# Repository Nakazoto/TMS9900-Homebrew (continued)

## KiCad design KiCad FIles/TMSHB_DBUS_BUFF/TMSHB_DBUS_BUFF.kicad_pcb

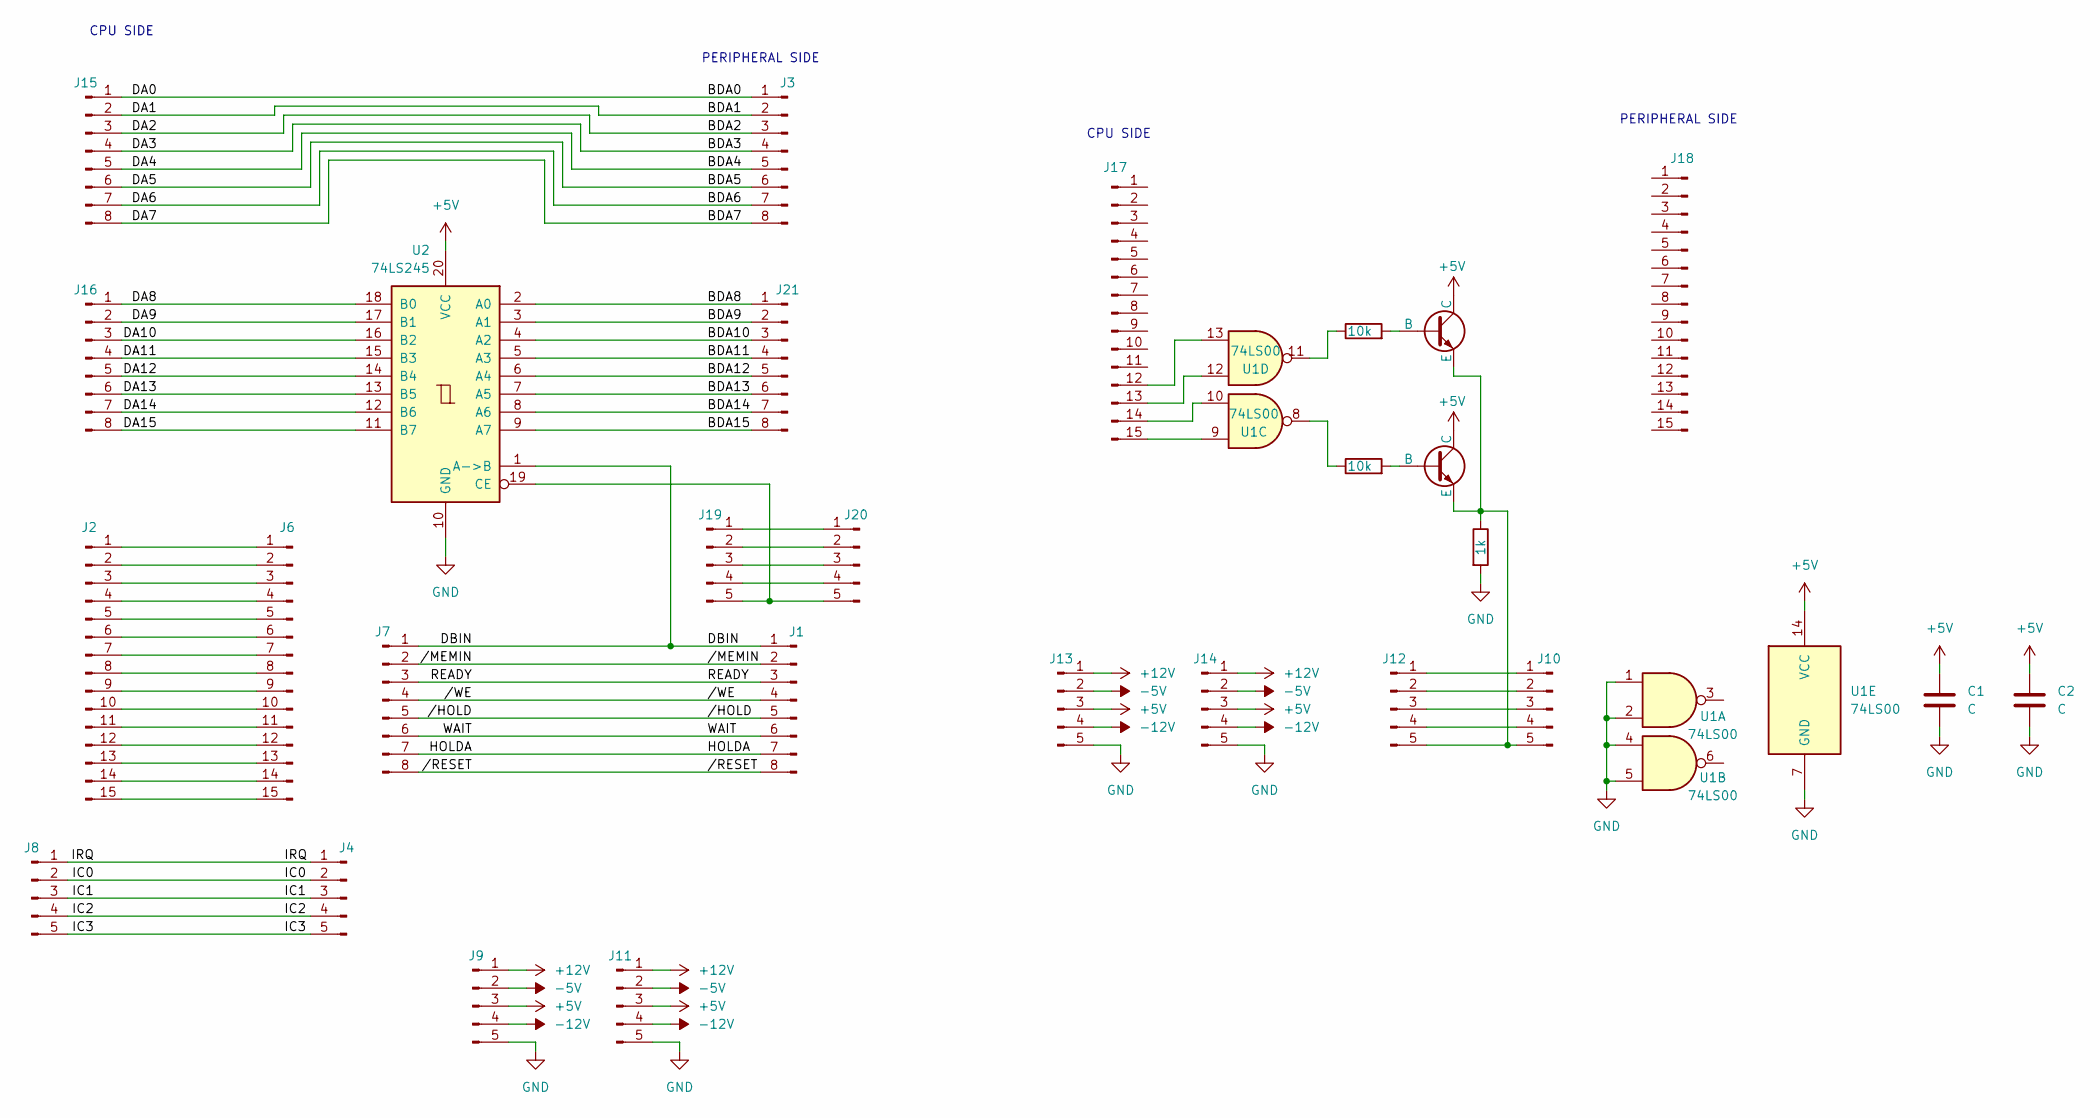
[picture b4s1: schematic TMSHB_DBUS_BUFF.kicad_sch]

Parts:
C1, C2: C; C_Disc_D3.0mm_W1.6mm_P2.50mm
J1, J3, J7, J15, J16, J21: Conn_01x08_Pin; PinHeader_1x08_P2.54mm_Vertical
J2, J6, J17, J18: Conn_01x15_Pin; PinHeader_1x15_P2.54mm_Vertical
J4, J8, J9, J10, J11, J12, J13, J14, J19, J20: Conn_01x05_Pin; PinHeader_1x05_P2.54mm_Vertical
Q1, Q3: NPN; TO-92_Inline_Wide
R1: 1k; R_Axial_DIN0207_L6.3mm_D2.5mm_P10.16mm_Horizontal
R2, R3: 10k; R_Axial_DIN0207_L6.3mm_D2.5mm_P10.16mm_Horizontal
U1: 74LS00; DIP-14_W7.62mm
U2: 74LS245; DIP-20_W7.62mm

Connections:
+5V: C1.1, C2.1, J9.3, J11.3, J13.3, J14.3, Q1.1 (C), Q3.1 (C), U1.14 (VCC), U2.20 (VCC)
+12V: J9.1, J11.1, J13.1, J14.1
-5V: J9.2, J11.2, J13.2, J14.2
-12V: J9.4, J11.4, J13.4, J14.4
/BDA0: J3.1, J15.1
/BDA1: J3.2, J15.2
/BDA2: J3.3, J15.3
/BDA3: J3.4, J15.4
/BDA4: J3.5, J15.5
/BDA5: J3.6, J15.6
/BDA6: J3.7, J15.7
/BDA7: J3.8, J15.8
/BDA8: J21.1, U2.2 (A0)
/BDA9: J21.2, U2.3 (A1)
/BDA10: J21.3, U2.4 (A2)
/BDA11: J21.4, U2.5 (A3)
/BDA12: J21.5, U2.6 (A4)
/BDA13: J21.6, U2.7 (A5)
/BDA14: J21.7, U2.8 (A6)
/BDA15: J21.8, U2.9 (A7)
/DA8: J16.1, U2.18 (B0)
/DA9: J16.2, U2.17 (B1)
/DA10: J16.3, U2.16 (B2)
/DA11: J16.4, U2.15 (B3)
/DA12: J16.5, U2.14 (B4)
/DA13: J16.6, U2.13 (B5)
/DA14: J16.7, U2.12 (B6)
/DA15: J16.8, U2.11 (B7)
/DBIN: J1.1, J7.1, U2.1 (A->B)
/HOLDA: J1.7, J7.7
/IC0: J4.2, J8.2
/IC1: J4.3, J8.3
/IC2: J4.4, J8.4
/IC3: J4.5, J8.5
/IRQ: J4.1, J8.1
/READY: J1.3, J7.3
/WAIT: J1.6, J7.6
//HOLD: J1.5, J7.5
//MEMIN: J1.2, J7.2
//RESET: J1.8, J7.8
//WE: J1.4, J7.4
GND: C1.2, C2.2, J9.5, J11.5, J13.5, J14.5, R1.2, U1.1, U1.2, U1.4, U1.5, U1.7 (GND), U2.10 (GND)
unnamed: J2.1, J6.1
unnamed: J2.2, J6.2
unnamed: J2.3, J6.3
unnamed: J2.4, J6.4
unnamed: J2.5, J6.5
unnamed: J2.6, J6.6
unnamed: J2.7, J6.7
unnamed: J2.8, J6.8
unnamed: J2.9, J6.9
unnamed: J2.10, J6.10
unnamed: J2.11, J6.11
unnamed: J2.12, J6.12
unnamed: J2.13, J6.13
unnamed: J2.14, J6.14
unnamed: J2.15, J6.15
unnamed: J10.1, J12.1
unnamed: J10.2, J12.2
unnamed: J10.3, J12.3
unnamed: J10.4, J12.4
unnamed: J10.5, J12.5, Q1.3 (E), Q3.3 (E), R1.1
unnamed: J17.12, U1.13
unnamed: J17.13, U1.12
unnamed: J17.14, U1.10
unnamed: J17.15, U1.9
unnamed: J19.1, J20.1
unnamed: J19.2, J20.2
unnamed: J19.3, J20.3
unnamed: J19.4, J20.4
unnamed: J19.5, J20.5, U2.19 (CE)
unnamed: Q1.2 (B), R3.2
unnamed: Q3.2 (B), R2.2
unnamed: R2.1, U1.11
unnamed: R3.1, U1.8

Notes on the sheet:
PERIPHERAL SIDE
CPU SIDE

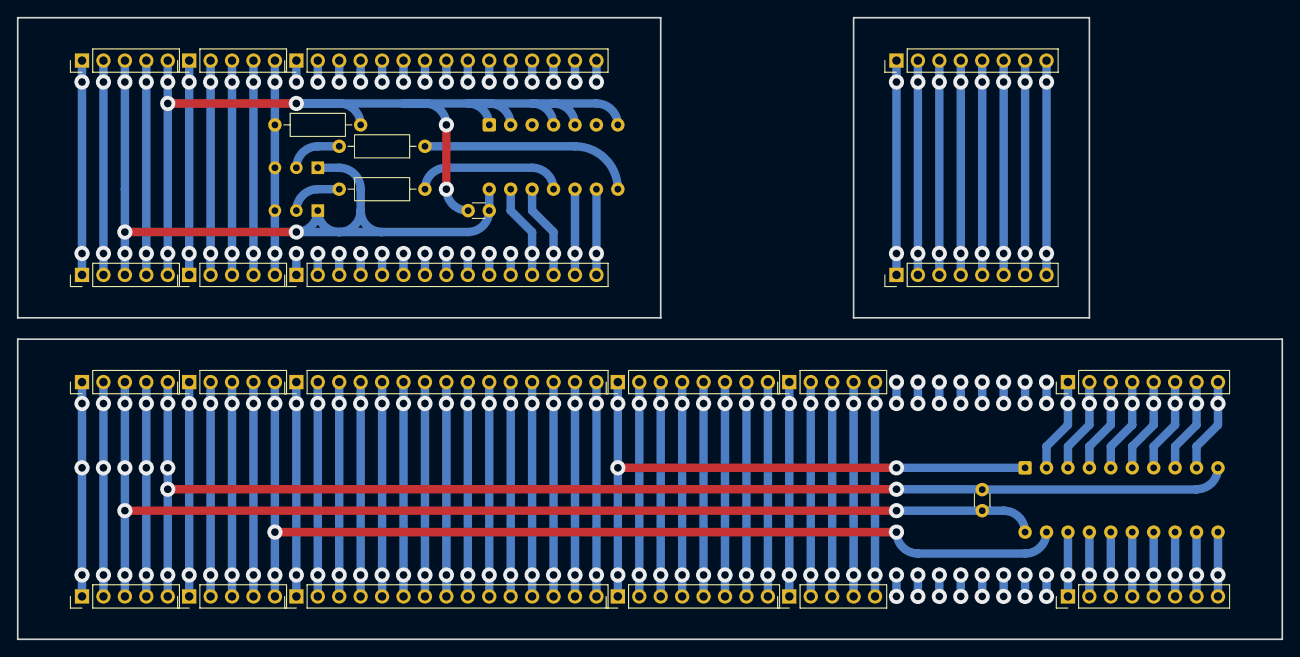
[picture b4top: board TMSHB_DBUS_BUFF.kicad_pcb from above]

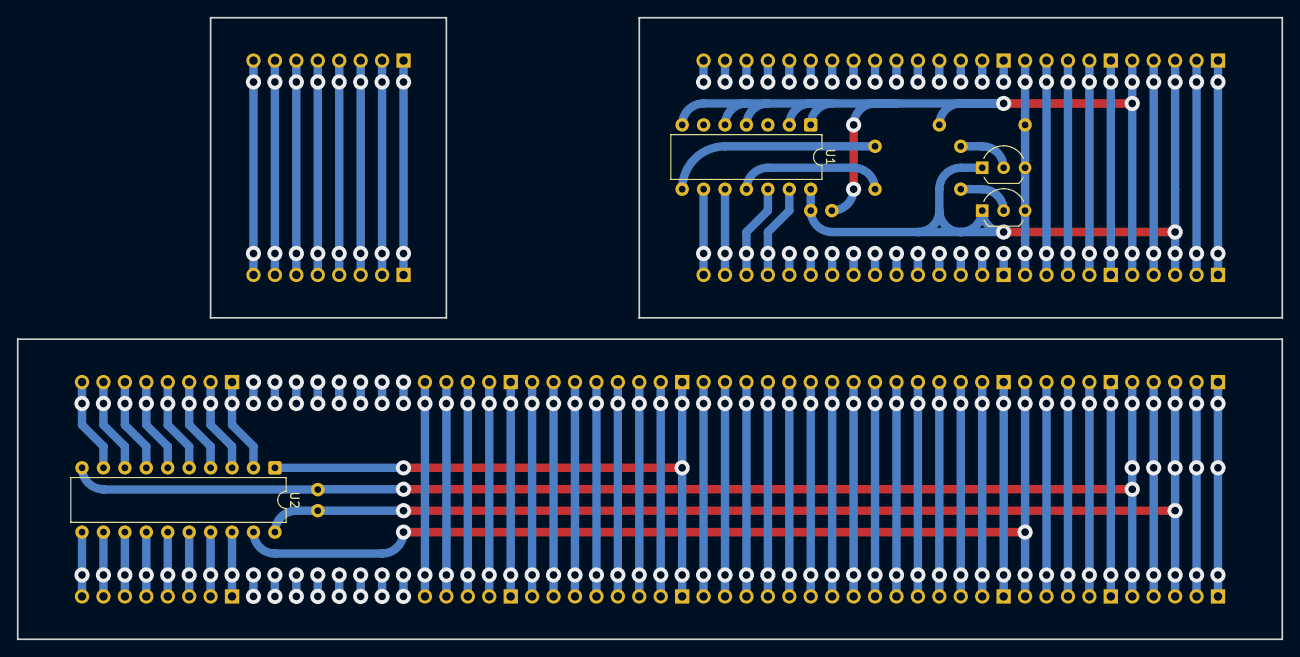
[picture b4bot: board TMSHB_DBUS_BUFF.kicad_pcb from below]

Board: 2 copper layers, 149.9 x 73.7 mm, 29 parts (4 on the bottom side), 75 nets.

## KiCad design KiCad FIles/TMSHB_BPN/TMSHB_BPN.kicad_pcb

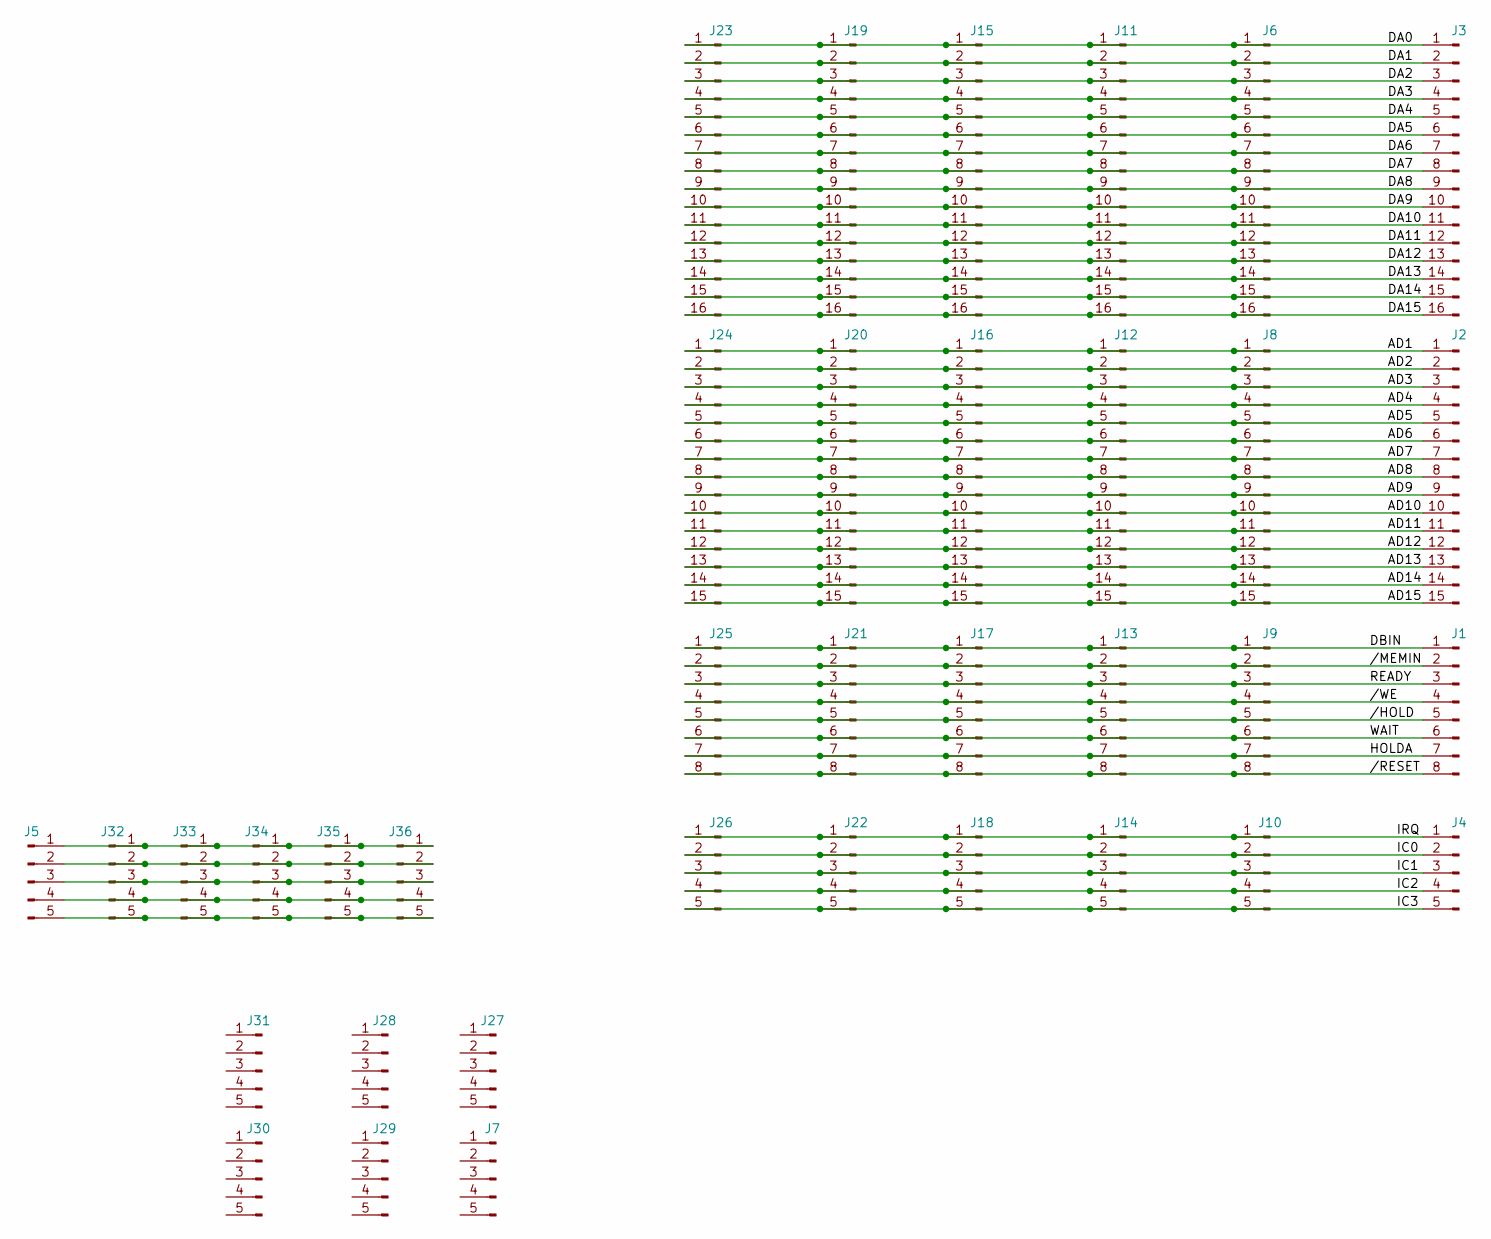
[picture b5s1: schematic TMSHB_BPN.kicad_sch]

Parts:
J1, J9, J13, J17, J21, J25: Conn_01x08_Pin; PinHeader_1x08_P2.54mm_Vertical
J2, J8, J12, J16, J20, J24: Conn_01x15_Pin; PinHeader_1x15_P2.54mm_Vertical
J3, J6, J11, J15, J19, J23: Conn_01x16_Pin; PinHeader_1x16_P2.54mm_Vertical
J4, J5, J7, J10, J14, J18, J22, J26, J27, J28, J29, J30, J31, J32, J33, J34, J35, J36: Conn_01x05_Pin; PinHeader_1x05_P2.54mm_Vertical

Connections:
/AD1: J2.1, J8.1, J12.1, J16.1, J20.1, J24.1
/AD2: J2.2, J8.2, J12.2, J16.2, J20.2, J24.2
/AD3: J2.3, J8.3, J12.3, J16.3, J20.3, J24.3
/AD4: J2.4, J8.4, J12.4, J16.4, J20.4, J24.4
/AD5: J2.5, J8.5, J12.5, J16.5, J20.5, J24.5
/AD6: J2.6, J8.6, J12.6, J16.6, J20.6, J24.6
/AD7: J2.7, J8.7, J12.7, J16.7, J20.7, J24.7
/AD8: J2.8, J8.8, J12.8, J16.8, J20.8, J24.8
/AD9: J2.9, J8.9, J12.9, J16.9, J20.9, J24.9
/AD10: J2.10, J8.10, J12.10, J16.10, J20.10, J24.10
/AD11: J2.11, J8.11, J12.11, J16.11, J20.11, J24.11
/AD12: J2.12, J8.12, J12.12, J16.12, J20.12, J24.12
/AD13: J2.13, J8.13, J12.13, J16.13, J20.13, J24.13
/AD14: J2.14, J8.14, J12.14, J16.14, J20.14, J24.14
/AD15: J2.15, J8.15, J12.15, J16.15, J20.15, J24.15
/DA0: J3.1, J6.1, J11.1, J15.1, J19.1, J23.1
/DA1: J3.2, J6.2, J11.2, J15.2, J19.2, J23.2
/DA2: J3.3, J6.3, J11.3, J15.3, J19.3, J23.3
/DA3: J3.4, J6.4, J11.4, J15.4, J19.4, J23.4
/DA4: J3.5, J6.5, J11.5, J15.5, J19.5, J23.5
/DA5: J3.6, J6.6, J11.6, J15.6, J19.6, J23.6
/DA6: J3.7, J6.7, J11.7, J15.7, J19.7, J23.7
/DA7: J3.8, J6.8, J11.8, J15.8, J19.8, J23.8
/DA8: J3.9, J6.9, J11.9, J15.9, J19.9, J23.9
/DA9: J3.10, J6.10, J11.10, J15.10, J19.10, J23.10
/DA10: J3.11, J6.11, J11.11, J15.11, J19.11, J23.11
/DA11: J3.12, J6.12, J11.12, J15.12, J19.12, J23.12
/DA12: J3.13, J6.13, J11.13, J15.13, J19.13, J23.13
/DA13: J3.14, J6.14, J11.14, J15.14, J19.14, J23.14
/DA14: J3.15, J6.15, J11.15, J15.15, J19.15, J23.15
/DA15: J3.16, J6.16, J11.16, J15.16, J19.16, J23.16
/DBIN: J1.1, J9.1, J13.1, J17.1, J21.1, J25.1
/HOLDA: J1.7, J9.7, J13.7, J17.7, J21.7, J25.7
/IC0: J4.2, J10.2, J14.2, J18.2, J22.2, J26.2
/IC1: J4.3, J10.3, J14.3, J18.3, J22.3, J26.3
/IC2: J4.4, J10.4, J14.4, J18.4, J22.4, J26.4
/IC3: J4.5, J10.5, J14.5, J18.5, J22.5, J26.5
/IRQ: J4.1, J10.1, J14.1, J18.1, J22.1, J26.1
/READY: J1.3, J9.3, J13.3, J17.3, J21.3, J25.3
/WAIT: J1.6, J9.6, J13.6, J17.6, J21.6, J25.6
//HOLD: J1.5, J9.5, J13.5, J17.5, J21.5, J25.5
//MEMIN: J1.2, J9.2, J13.2, J17.2, J21.2, J25.2
//RESET: J1.8, J9.8, J13.8, J17.8, J21.8, J25.8
//WE: J1.4, J9.4, J13.4, J17.4, J21.4, J25.4
unnamed: J5.1, J32.1, J33.1, J34.1, J35.1, J36.1
unnamed: J5.2, J32.2, J33.2, J34.2, J35.2, J36.2
unnamed: J5.3, J32.3, J33.3, J34.3, J35.3, J36.3
unnamed: J5.4, J32.4, J33.4, J34.4, J35.4, J36.4
unnamed: J5.5, J32.5, J33.5, J34.5, J35.5, J36.5

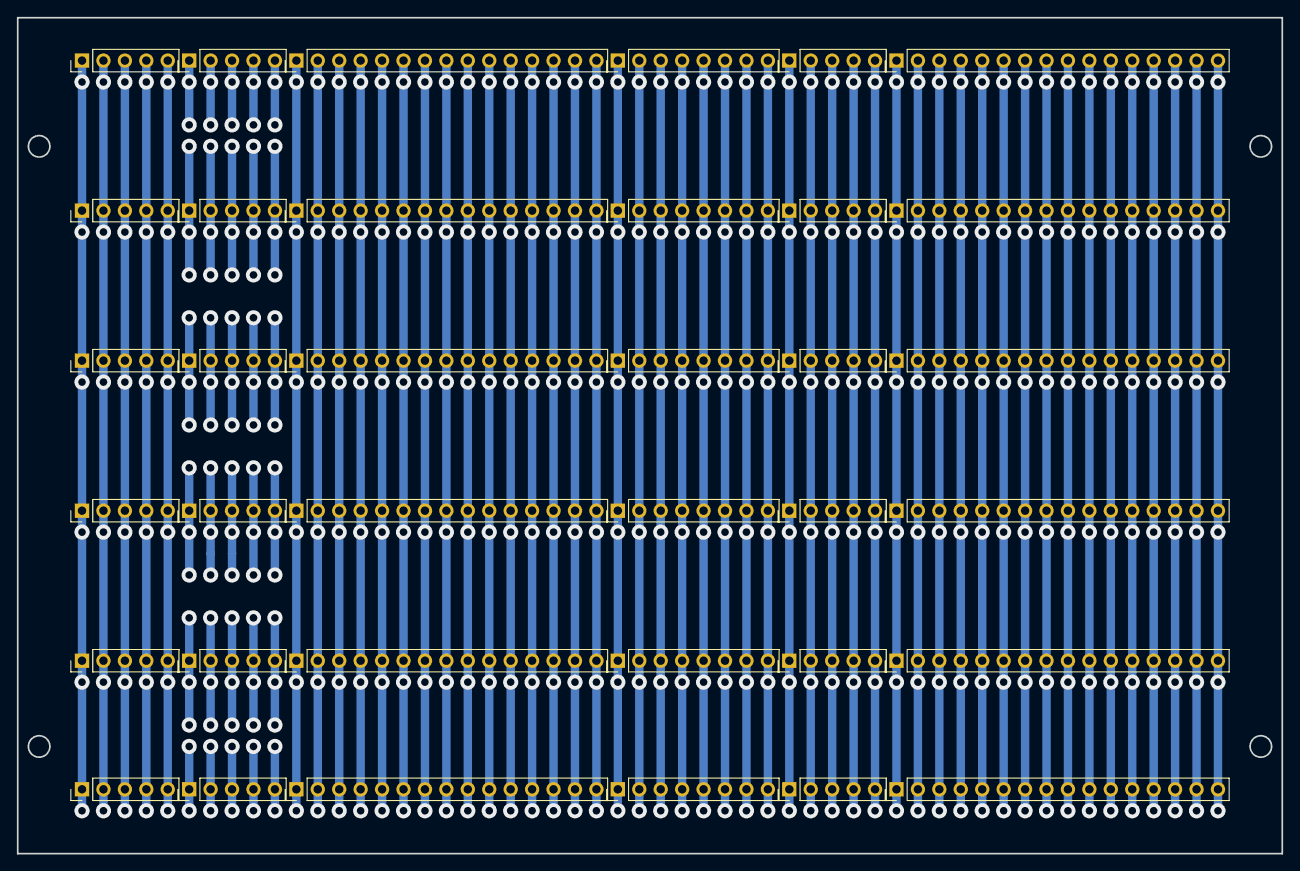
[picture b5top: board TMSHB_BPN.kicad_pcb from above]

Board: 2 copper layers, 149.9 x 99.1 mm, 36 parts (0 on the bottom side), 49 nets.

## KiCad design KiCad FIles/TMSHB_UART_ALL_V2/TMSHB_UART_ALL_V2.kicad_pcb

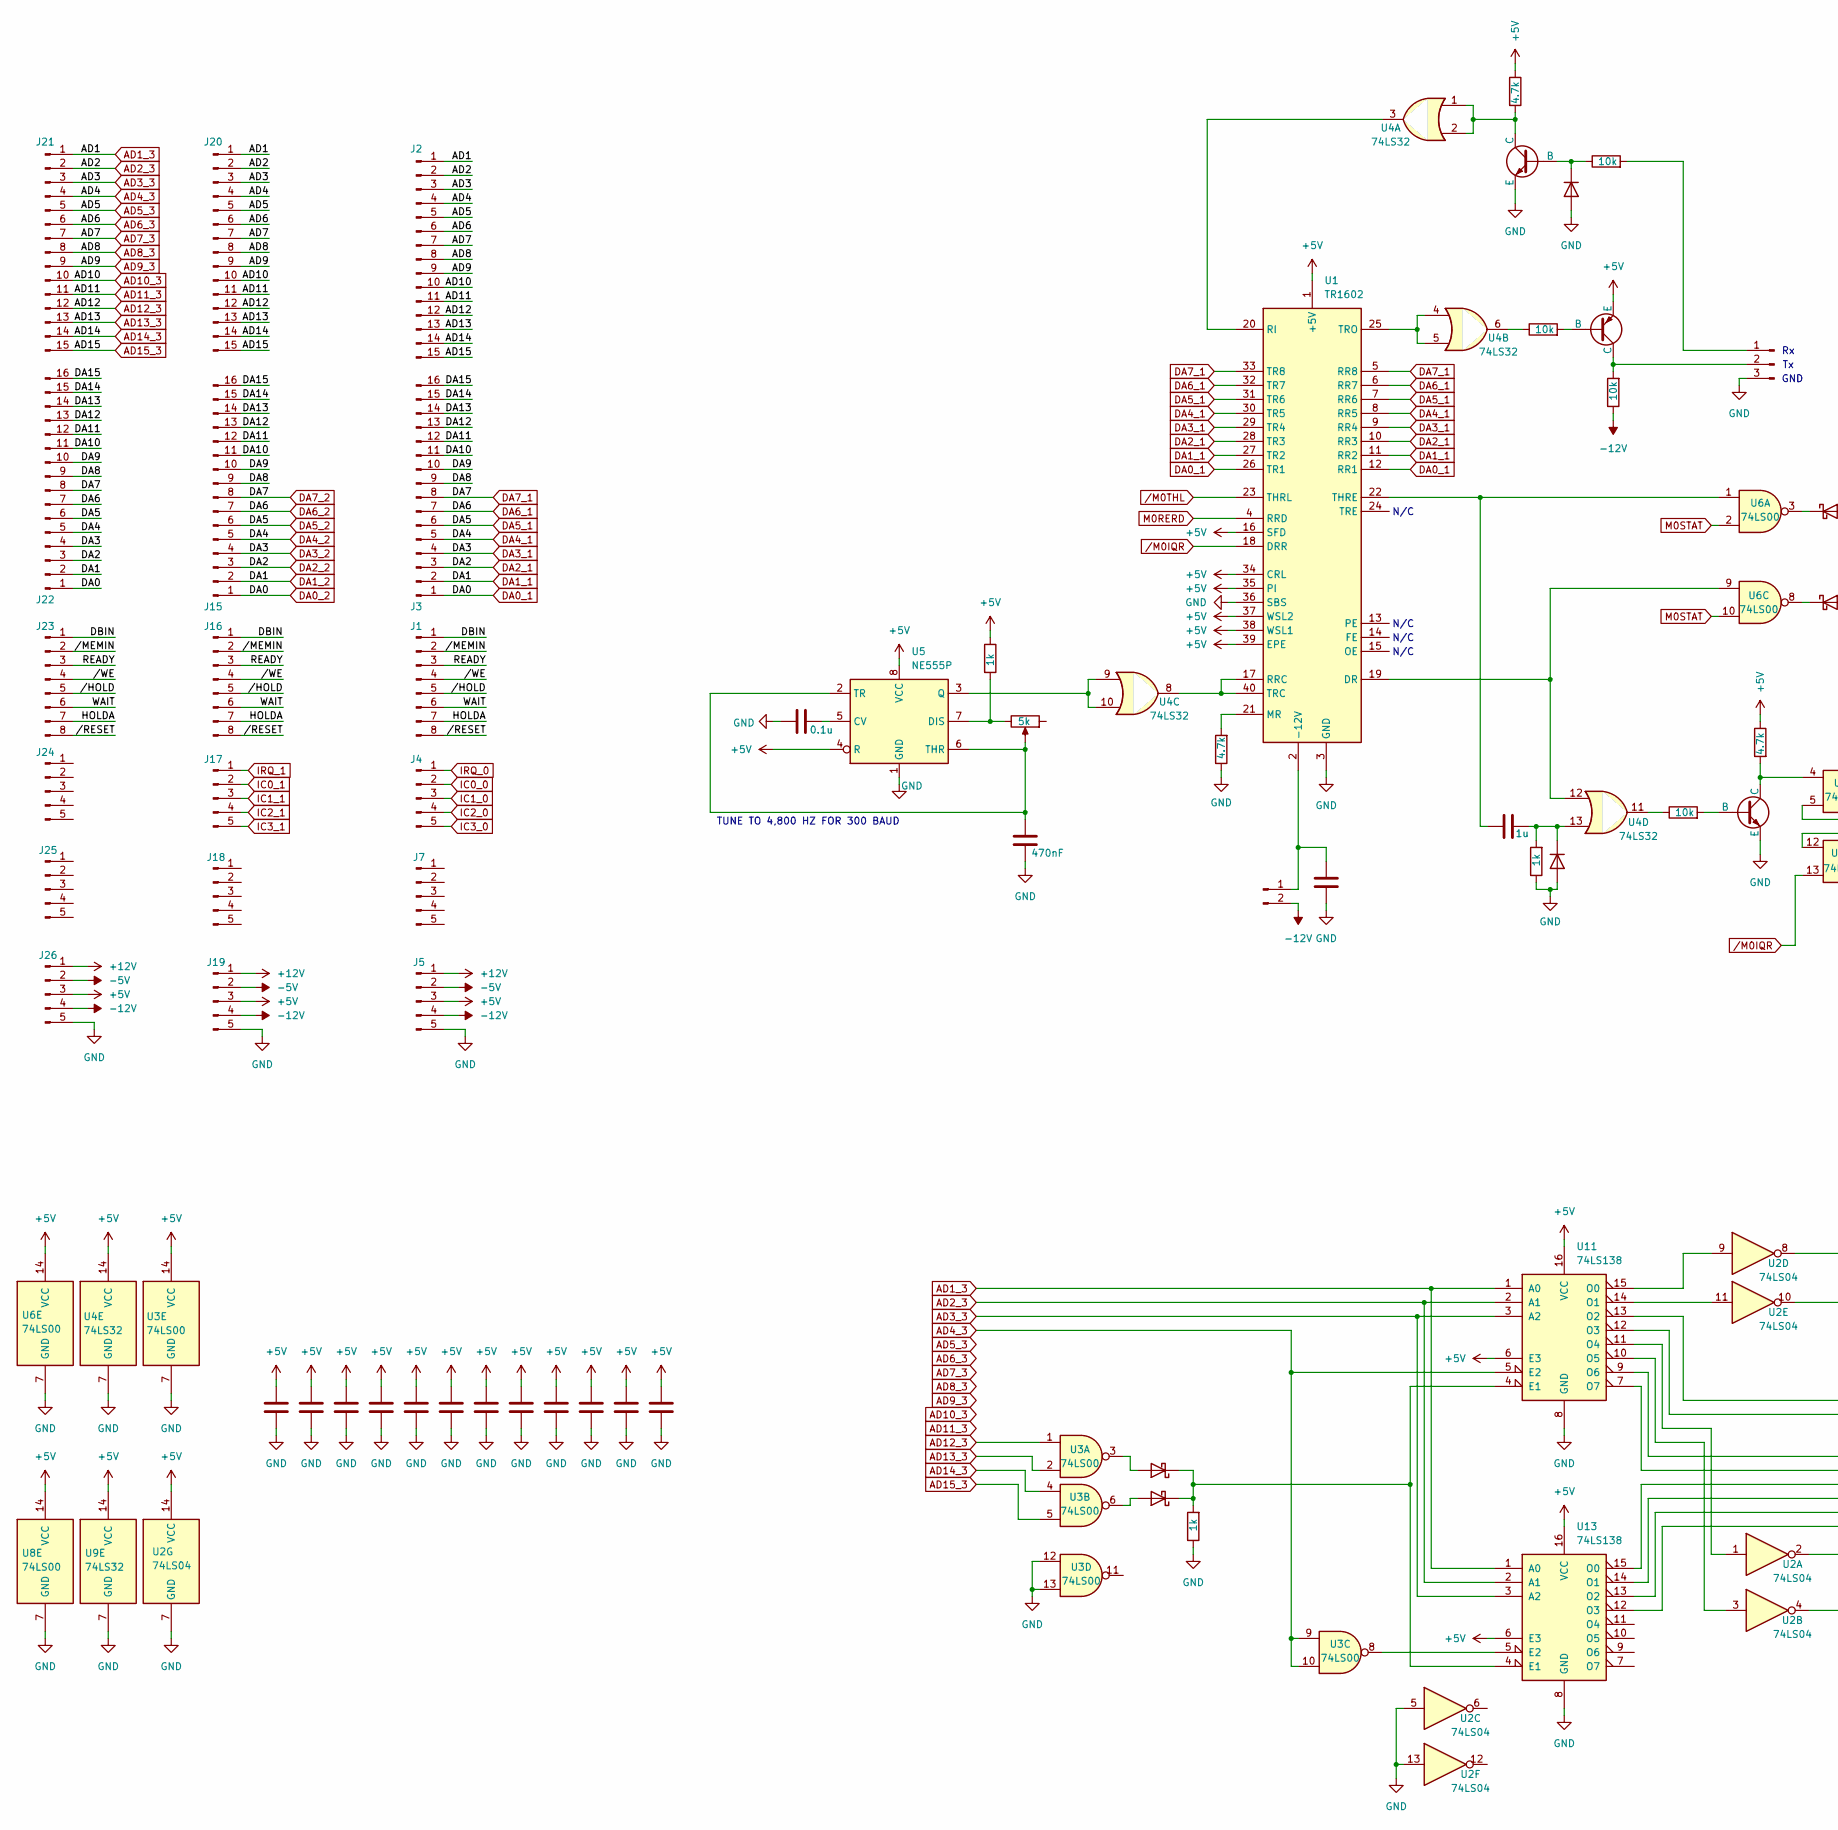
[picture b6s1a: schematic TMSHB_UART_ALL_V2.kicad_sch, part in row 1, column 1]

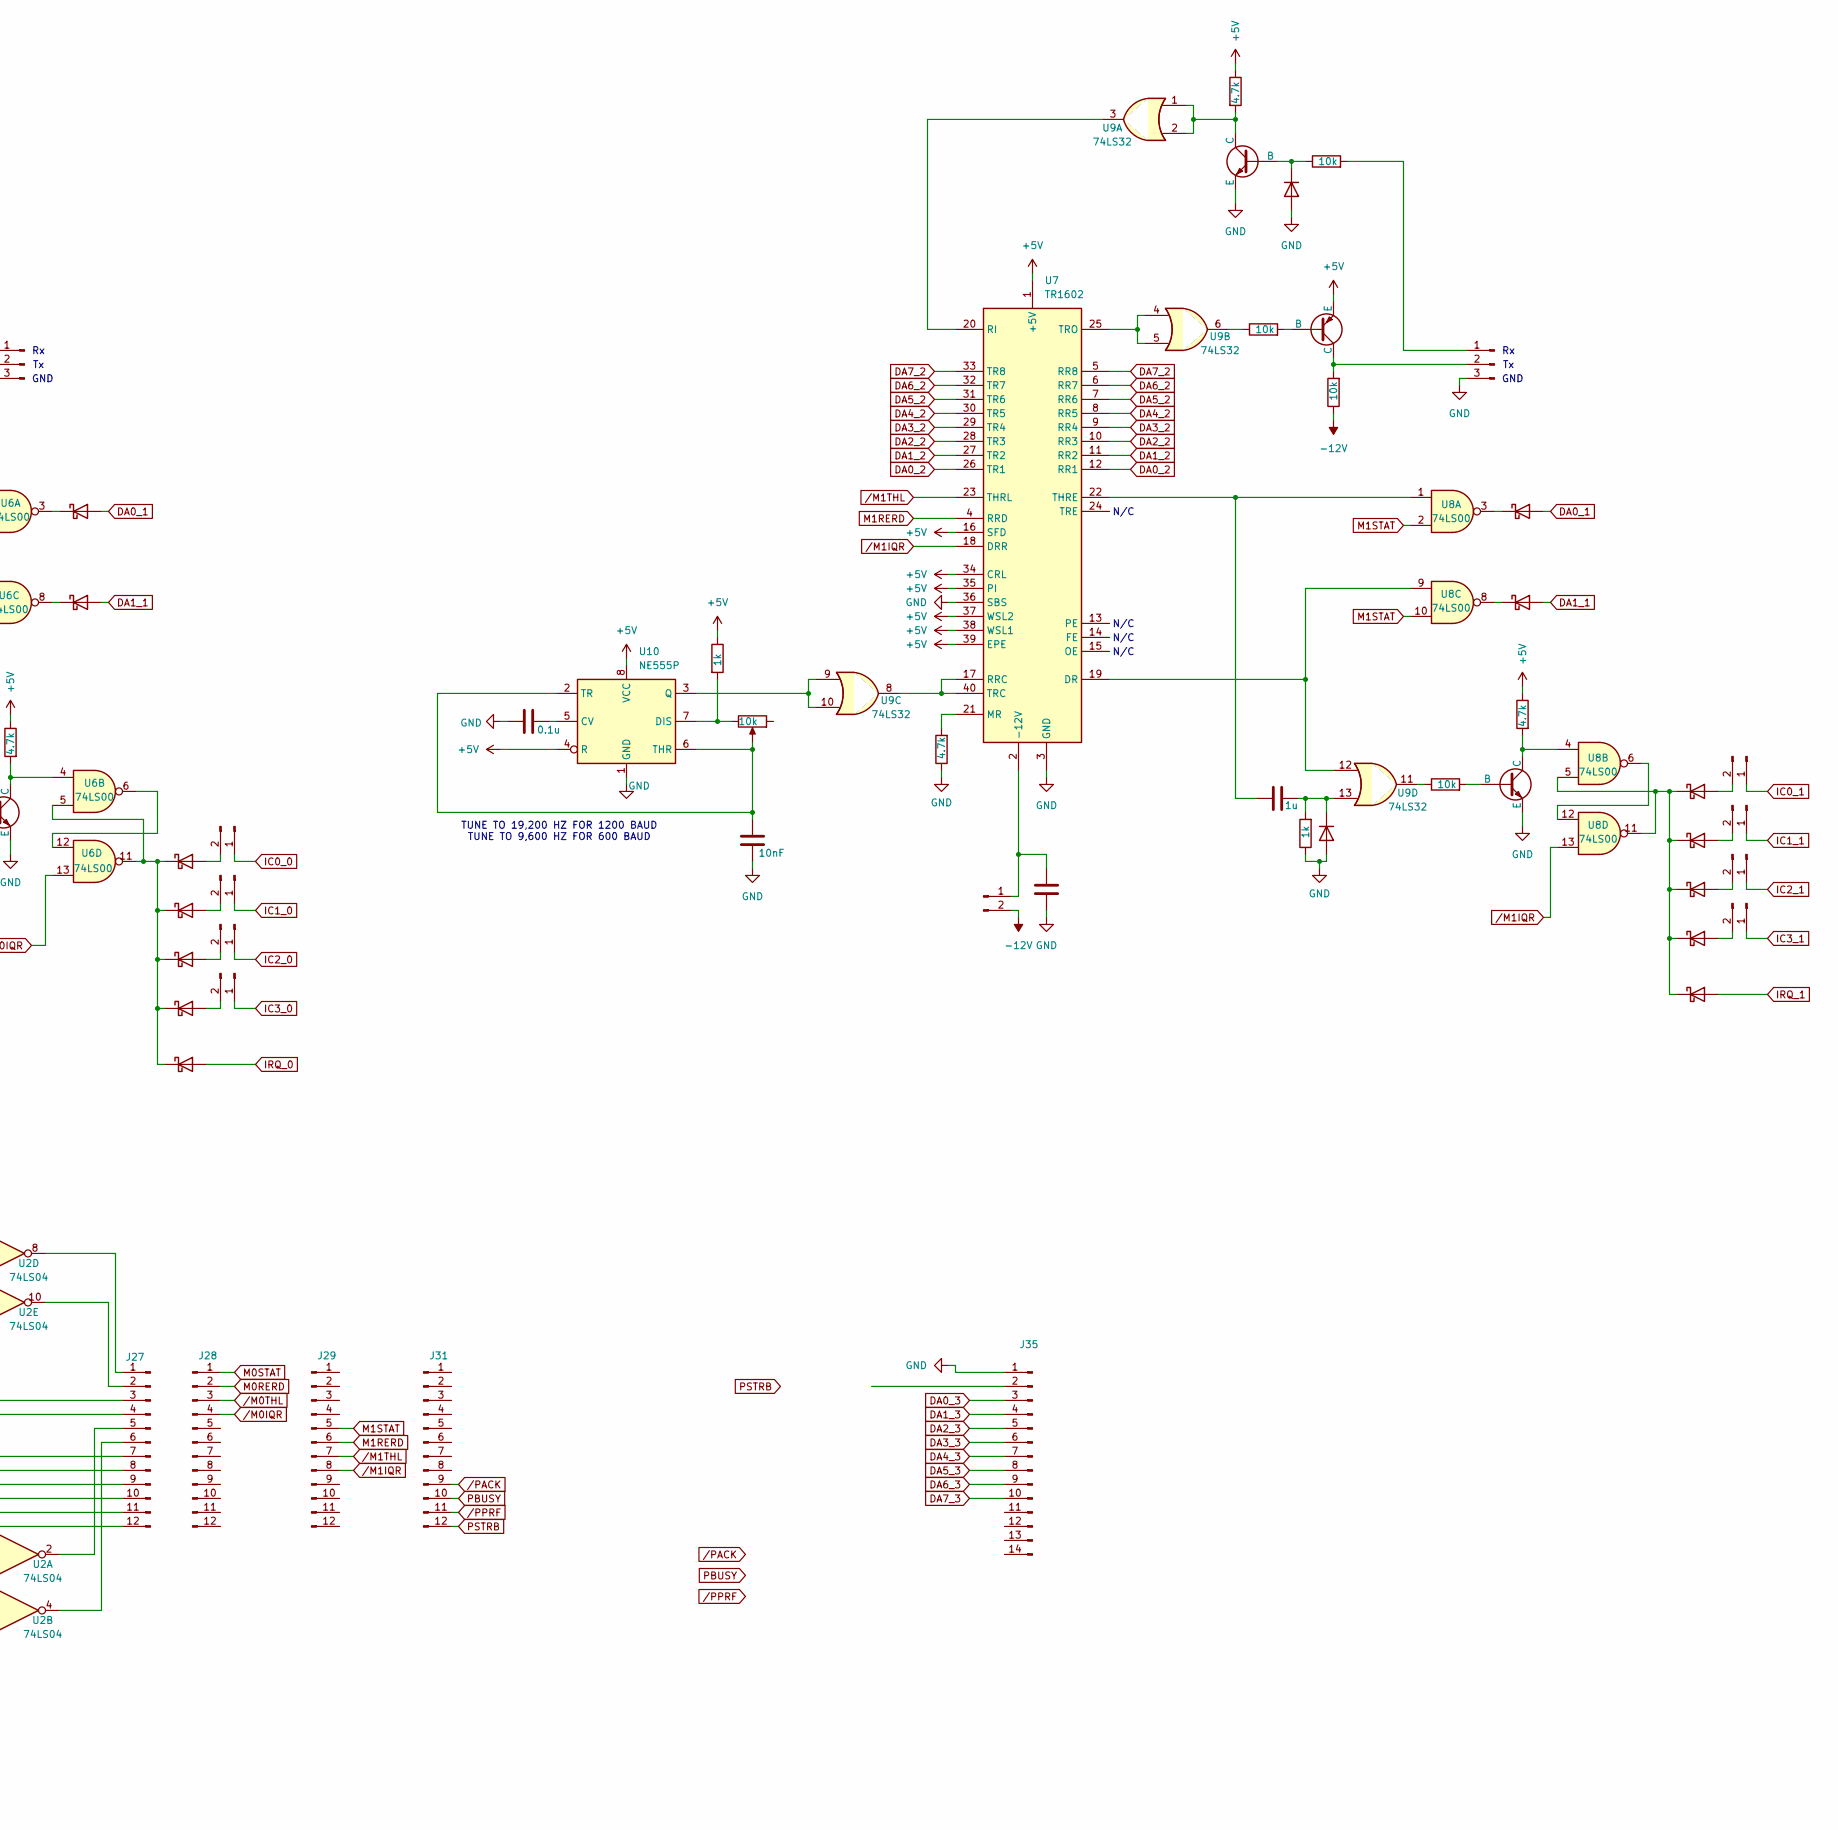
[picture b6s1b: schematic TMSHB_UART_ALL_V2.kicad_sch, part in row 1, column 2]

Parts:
C1, C2, C3, C6, C9, C10, C11, C12, C13, C14, C15, C16, C17, C21: C; C_Disc_D3.0mm_W1.6mm_P2.50mm
C4: 470nF; C_Disc_D3.0mm_W1.6mm_P2.50mm
C5, C7: 0.1u; C_Disc_D3.0mm_W1.6mm_P2.50mm
C8: 10nF; C_Disc_D3.0mm_W1.6mm_P2.50mm
C19, C20: 1u; C_Disc_D3.0mm_W1.6mm_P2.50mm
D1, D2, D3, D18: D; D_DO-34_SOD68_P7.62mm_Horizontal
D4, D5, D6, D7, D8, D9, D10, D11, D12, D13, D14, D15, D16, D17, D19, D20: D_Schottky; D_DO-34_SOD68_P7.62mm_Horizontal
J1, J16, J23: Conn_01x08_Pin; PinHeader_1x08_P2.54mm_Vertical
J2, J20, J21: Conn_01x15_Pin; PinHeader_1x15_P2.54mm_Vertical
J3, J15, J22: Conn_01x16_Pin; PinHeader_1x16_P2.54mm_Vertical
J4, J5, J7, J17, J18, J19, J24, J25, J26: Conn_01x05_Pin; PinHeader_1x05_P2.54mm_Vertical
J6, J8: Conn_01x03_Pin; PinHeader_1x03_P2.54mm_Vertical
J9, J10, J11, J12, J13, J14, J30, J32, J33, J34: Conn_01x02_Pin; PinHeader_1x02_P2.54mm_Vertical
J27, J28, J29, J31: Conn_01x12_Pin; PinHeader_1x12_P2.54mm_Vertical
J35: Conn_01x14_Pin
Q1, Q3, Q4, Q13: NPN; TO-92_Inline_Wide
Q2, Q14: PNP; TO-92_Inline_Wide
R1, R3, R9, R11, R16, R22: 4.7k; R_Axial_DIN0207_L6.3mm_D2.5mm_P10.16mm_Horizontal
R2, R4, R8, R13, R26: 1k; R_Axial_DIN0207_L6.3mm_D2.5mm_P10.16mm_Horizontal
R5, R6, R7, R10, R12, R23, R24, R25: 10k; R_Axial_DIN0207_L6.3mm_D2.5mm_P10.16mm_Horizontal
RV1: 5k; Potentiometer_Bourns_3296W_Vertical
RV2: 10k; Potentiometer_Bourns_3296W_Vertical
U1, U7: TR1602; DIP-40_W15.24mm
U2: 74LS04; DIP-14_W7.62mm
U3, U6, U8: 74LS00; DIP-14_W7.62mm
U4, U9: 74LS32; DIP-14_W7.62mm
U5, U10: NE555P; DIP-8_W7.62mm
U11, U13: 74LS138; DIP-16_W7.62mm

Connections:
+5V: C1.1, C2.1, C3.1, C6.1, C9.1, C10.1, C11.1, C12.1, C13.1, C14.1, C15.1, C16.1, J5.3, J19.3, J26.3, Q2.3 (E), Q14.3 (E), R1.1, R4.1, R9.1, R11.1, R22.1, R26.1, U1.1 (+5V), U1.16 (SFD), U1.34 (CRL), U1.35 (PI), U1.37 (WSL2), U1.38 (WSL1), U1.39 (EPE), U2.14 (VCC), U3.14 (VCC), U4.14 (VCC), U5.4 (R), U5.8 (VCC), U6.14 (VCC), U7.1 (+5V), U7.16 (SFD), U7.34 (CRL), U7.35 (PI), U7.37 (WSL2), U7.38 (WSL1), U7.39 (EPE), U8.14 (VCC), U9.14 (VCC), U10.4 (R), U10.8 (VCC), U11.6 (E3), U11.16 (VCC), U13.6 (E3), U13.16 (VCC)
+12V: J5.1, J19.1, J26.1
-5V: J5.2, J19.2, J26.2
-12V: J5.4, J19.4, J26.4, J32.2, J34.2, R7.1, R25.1
/DA8: J3.9, J15.9, J22.9
/DA9: J3.10, J15.10, J22.10
/DA10: J3.11, J15.11, J22.11
/DA11: J3.12, J15.12, J22.12
/DA12: J3.13, J15.13, J22.13
/DA13: J3.14, J15.14, J22.14
/DA14: J3.15, J15.15, J22.15
/DA15: J3.16, J15.16, J22.16
/DBIN: J1.1, J16.1, J23.1
/HOLDA: J1.7, J16.7, J23.7
/READY: J1.3, J16.3, J23.3
/WAIT: J1.6, J16.6, J23.6
//HOLD: J1.5, J16.5, J23.5
//MEMIN: J1.2, J16.2, J23.2
//RESET: J1.8, J16.8, J23.8
//WE: J1.4, J16.4, J23.4
AD1_3: J2.1, J20.1, J21.1, U11.1 (A0), U13.1 (A0)
AD2_3: J2.2, J20.2, J21.2, U11.2 (A1), U13.2 (A1)
AD3_3: J2.3, J20.3, J21.3, U11.3 (A2), U13.3 (A2)
AD4_3: J2.4, J20.4, J21.4, U3.9, U3.10, U11.5 (E2)
AD5_3: J2.5, J20.5, J21.5
AD6_3: J2.6, J20.6, J21.6
AD7_3: J2.7, J20.7, J21.7
AD8_3: J2.8, J20.8, J21.8
AD9_3: J2.9, J20.9, J21.9
AD10_3: J2.10, J20.10, J21.10
AD11_3: J2.11, J20.11, J21.11
AD12_3: J2.12, J20.12, J21.12, U3.1
AD13_3: J2.13, J20.13, J21.13, U3.2
AD14_3: J2.14, J20.14, J21.14, U3.4
AD15_3: J2.15, J20.15, J21.15, U3.5
DA0_1: D4.2 (A), D19.2 (A), J3.1, J15.1, J22.1, U1.12 (RR1), U1.26 (TR1), U7.12 (RR1), U7.26 (TR1)
DA1_1: D5.2 (A), D20.2 (A), J3.2, J15.2, J22.2, U1.11 (RR2), U1.27 (TR2), U7.11 (RR2), U7.27 (TR2)
DA2_1: J3.3, J15.3, J22.3, U1.10 (RR3), U1.28 (TR3), U7.10 (RR3), U7.28 (TR3)
DA3_1: J3.4, J15.4, J22.4, U1.9 (RR4), U1.29 (TR4), U7.9 (RR4), U7.29 (TR4)
DA4_1: J3.5, J15.5, J22.5, U1.8 (RR5), U1.30 (TR5), U7.8 (RR5), U7.30 (TR5)
DA5_1: J3.6, J15.6, J22.6, U1.7 (RR6), U1.31 (TR6), U7.7 (RR6), U7.31 (TR6)
DA6_1: J3.7, J15.7, J22.7, U1.6 (RR7), U1.32 (TR7), U7.6 (RR7), U7.32 (TR7)
DA7_1: J3.8, J15.8, J22.8, U1.5 (RR8), U1.33 (TR8), U7.5 (RR8), U7.33 (TR8)
GND: C1.2, C2.2, C3.2, C4.2, C5.1, C6.2, C7.1, C8.2, C9.2, C10.2, C11.2, C12.2, C13.2, C14.2, C15.2, C16.2, C17.2, C21.2, D1.2 (A), D2.2 (A), D3.2 (A), D18.2 (A), J5.5, J6.3, J8.3, J19.5, J26.5, J35.1, Q1.3 (E), Q3.3 (E), Q4.3 (E), Q13.3 (E), R2.1, R3.1, R8.1, R13.1, R16.1, U1.3 (GND), U1.36 (SBS), U2.5, U2.7 (GND), U2.13, U3.7 (GND), U3.12, U3.13, U4.7 (GND), U5.1 (GND), U6.7 (GND), U7.3 (GND), U7.36 (SBS), U8.7 (GND), U9.7 (GND), U10.1 (GND), U11.8 (GND), U13.8 (GND)
IC0_0: J4.2, J11.1
IC0_1: J12.1, J17.2
IC1_0: J4.3, J10.1
IC1_1: J13.1, J17.3
IC2_0: J4.4, J9.1
IC2_1: J14.1, J17.4
IC3_0: J4.5, J30.1
IC3_1: J17.5, J33.1
IRQ_0: D10.2 (A), J4.1
IRQ_1: D17.2 (A), J17.1
M0RERD: J28.2, U1.4 (RRD)
M0STAT: J28.1, U6.2, U6.10
M1RERD: J29.6, U7.4 (RRD)
M1STAT: J29.5, U8.2, U8.10
unnamed: D1.1 (K), Q3.2 (B), R10.1
unnamed: D2.1 (K), Q13.2 (B), R24.1
unnamed: C19.2, D3.1 (K), R2.2, U4.13
unnamed: D4.1 (K), U6.3
unnamed: D5.1 (K), U6.8
unnamed: D6.2 (A), J11.2
unnamed: D7.2 (A), J10.2
unnamed: D8.2 (A), J9.2
unnamed: D9.2 (A), J30.2
unnamed: D6.1 (K), D7.1 (K), D8.1 (K), D9.1 (K), D10.1 (K), U6.5, U6.11
unnamed: D11.2 (A), U3.3
unnamed: D11.1 (K), D12.1 (K), R8.2, U11.4 (E1), U13.4 (E1)
unnamed: D12.2 (A), U3.6
unnamed: D13.2 (A), J12.2
unnamed: D13.1 (K), D14.1 (K), D15.1 (K), D16.1 (K), D17.1 (K), U8.5, U8.11
unnamed: D14.2 (A), J13.2
unnamed: D15.2 (A), J14.2
unnamed: D16.2 (A), J33.2
unnamed: C20.2, D18.1 (K), R13.2, U9.13
unnamed: D19.1 (K), U8.3
unnamed: D20.1 (K), U8.8
unnamed: J6.1, R10.2
unnamed: J6.2, Q2.1 (C), R7.2
unnamed: J8.1, R24.2
unnamed: J8.2, Q14.1 (C), R25.2
unnamed: J27.1, U2.8
unnamed: J27.2, U2.10
unnamed: J27.3, U11.13 (O2)
unnamed: J27.4, U11.12 (O3)
unnamed: J27.5, U2.2
unnamed: J27.6, U2.4
unnamed: J27.7, U11.9 (O6)
unnamed: J27.8, U11.7 (O7)
unnamed: J27.9, U13.15 (O0)
unnamed: J27.10, U13.14 (O1)
unnamed: J27.11, U13.13 (O2)
unnamed: J27.12, U13.12 (O3)
unnamed: C17.1, J32.1, U1.2 (-12V)
unnamed: C21.1, J34.1, U7.2 (-12V)
unnamed: Q1.2 (B), R5.2
unnamed: Q1.1 (C), R1.2, U6.4
unnamed: Q2.2 (B), R6.2
unnamed: Q3.1 (C), R11.2, U4.1, U4.2
unnamed: Q4.2 (B), R12.2
unnamed: Q4.1 (C), R9.2, U8.4
unnamed: Q13.1 (C), R22.2, U9.1, U9.2
unnamed: Q14.2 (B), R23.2
unnamed: R5.1, U4.11
unnamed: R6.1, U4.6
unnamed: R12.1, U9.11
unnamed: R23.1, U9.6
unnamed: U1.19 (DR), U4.12, U6.9
unnamed: R3.2, U1.21 (MR)
unnamed: U1.20 (RI), U4.3
unnamed: U1.17 (RRC), U1.40 (TRC), U4.8
unnamed: C19.1, U1.22 (THRE), U6.1
unnamed: U1.25 (TRO), U4.4, U4.5
unnamed: C5.2, U5.5 (CV)
unnamed: R4.2, RV1.3, U5.7 (DIS)
unnamed: U4.9, U4.10, U5.3 (Q)
unnamed: C4.1, RV1.2, U5.2 (TR), U5.6 (THR)
unnamed: U6.6, U6.12
unnamed: U7.19 (DR), U8.9, U9.12
unnamed: R16.2, U7.21 (MR)
unnamed: U7.20 (RI), U9.3
unnamed: U7.17 (RRC), U7.40 (TRC), U9.8
unnamed: C20.1, U7.22 (THRE), U8.1
unnamed: U7.25 (TRO), U9.4, U9.5
unnamed: U8.6, U8.12
unnamed: C7.2, U10.5 (CV)
unnamed: R26.2, RV2.3, U10.7 (DIS)
unnamed: U9.9, U9.10, U10.3 (Q)
unnamed: C8.1, RV2.2, U10.2 (TR), U10.6 (THR)
unnamed: U2.9, U11.15 (O0)
unnamed: U2.11, U11.14 (O1)
unnamed: U2.1, U11.11 (O4)
unnamed: U2.3, U11.10 (O5)
unnamed: U3.8, U13.5 (E2)
PBUSY: J31.10
PSTRB: J31.12
/M0IQR: J28.4, U1.18 (DRR), U6.13
/M0THL: J28.3, U1.23 (THRL)
/M1IQR: J29.8, U7.18 (DRR), U8.13
/M1THL: J29.7, U7.23 (THRL)
/PACK: J31.9
/PPRF: J31.11

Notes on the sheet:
GND
TUNE TO 19,200 HZ FOR 1200 BAUD TUNE TO 9,600 HZ FOR 600 BAUD
N/C
TUNE TO 4,800 HZ FOR 300 BAUD

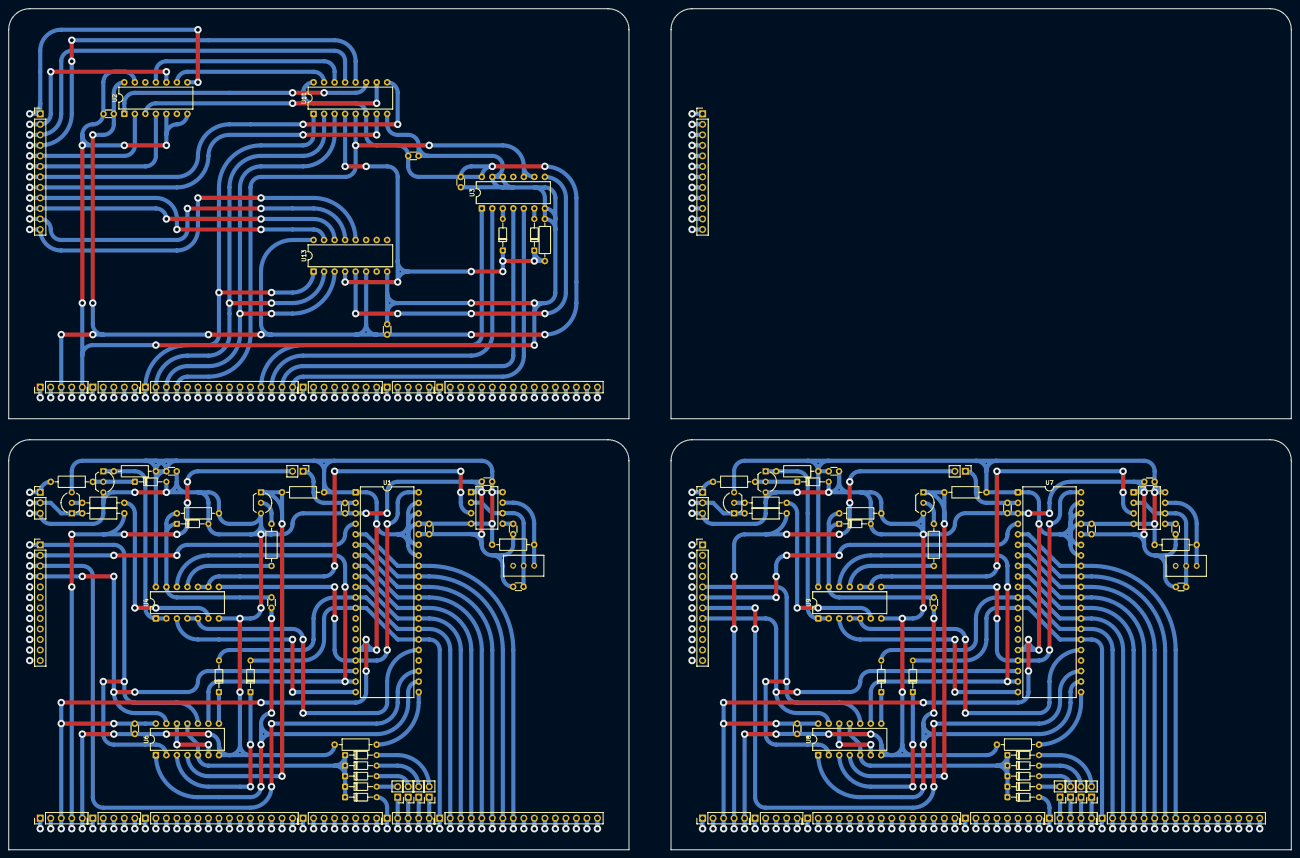
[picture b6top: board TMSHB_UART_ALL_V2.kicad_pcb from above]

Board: 2 copper layers, 309.9 x 203.2 mm, 113 parts (0 on the bottom side), 140 nets.
